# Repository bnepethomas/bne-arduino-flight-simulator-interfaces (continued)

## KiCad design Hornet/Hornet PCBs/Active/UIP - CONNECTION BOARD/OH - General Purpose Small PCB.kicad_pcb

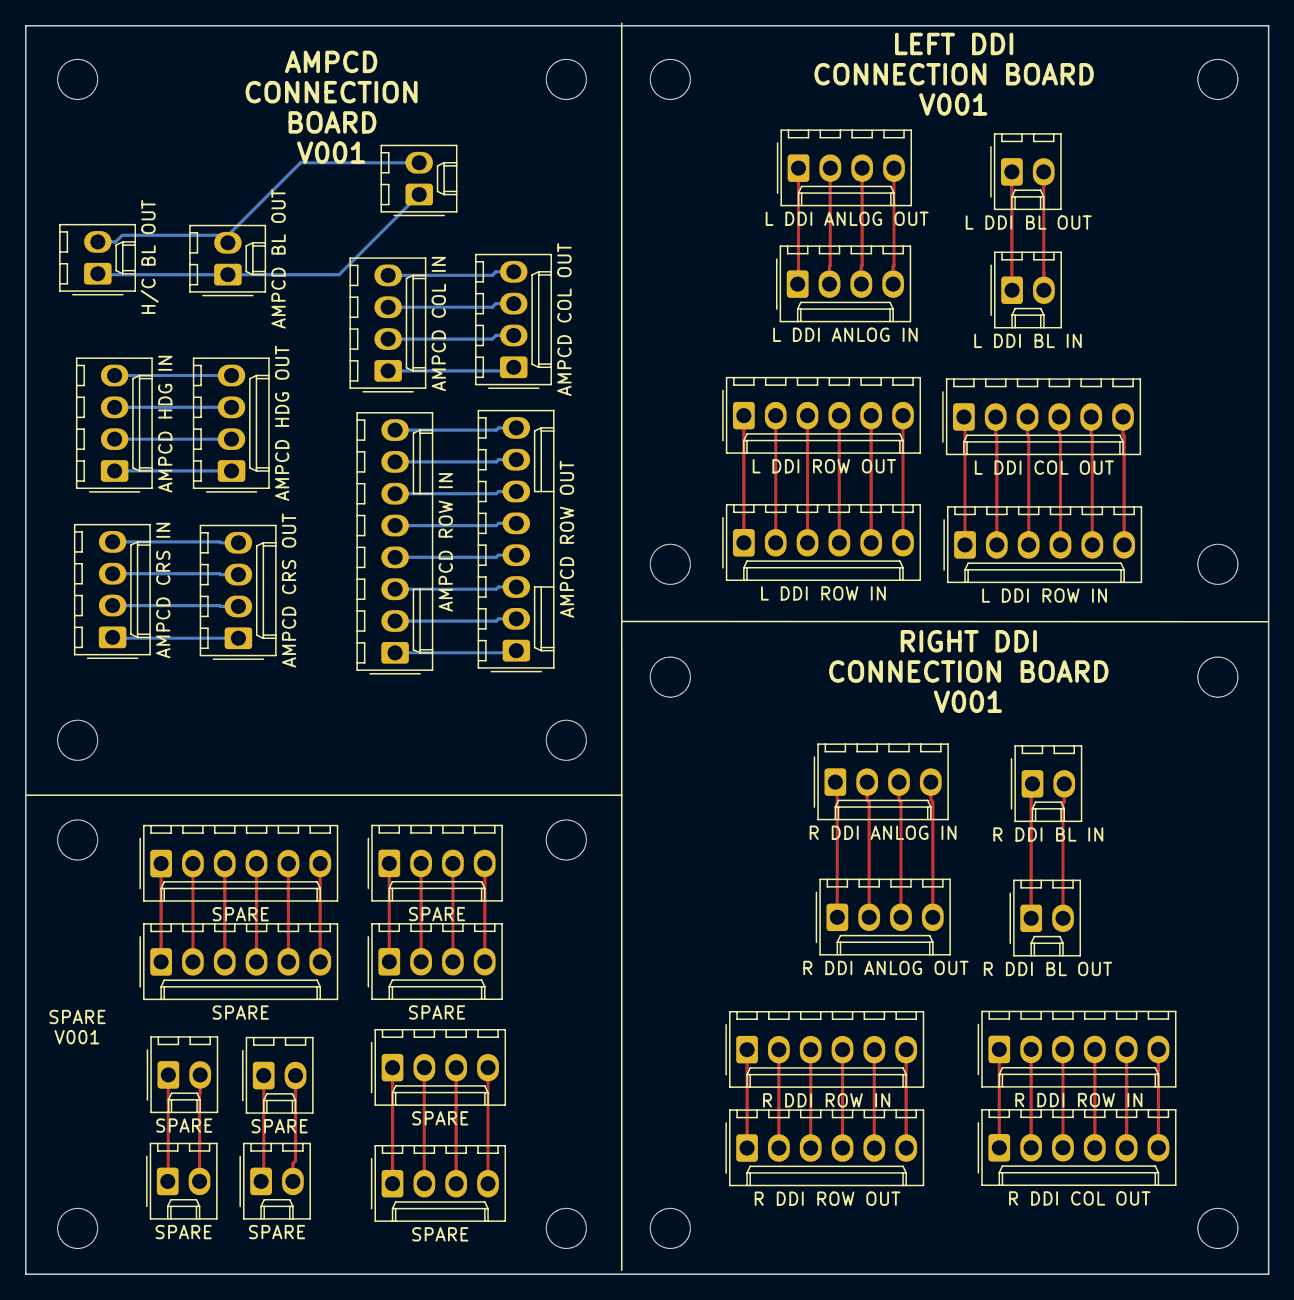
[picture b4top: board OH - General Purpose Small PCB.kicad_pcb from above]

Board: 2 copper layers, 99.2 x 99.6 mm, 53 parts (0 on the bottom side), 76 nets.

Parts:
H1, H2, H3, H4, H5, H6, H7, H8, H9, H10, H11, H12, H13, H14, H15, H16: MountingHole; MountingHole_3.2mm_M3
J1: AMPCD COL IN; Molex_1x04_P2.54mm_Vertical
J2: AMPCD COL OUT; Molex_1x04_P2.54mm_Vertical
J3: H/C BL OUT; Molex_1x02_P2.54mm_Vertical
J4, J12, J34, J37: SPARE; Molex_1x02_P2.54mm_Vertical
J5: AMPCD CRS IN; Molex_1x04_P2.54mm_Vertical
J6: AMPCD HDG IN; Molex_1x04_P2.54mm_Vertical
J7, J8, J14, J16: SPARE; Molex_1x04_P2.54mm_Vertical
J9: AMPCD BL IN; Molex_1x02_P2.54mm_Vertical
J10, J18: SPARE; Molex_1x06_P2.54mm_Vertical
J11: L DDI ANLOG IN; Molex_1x04_P2.54mm_Vertical
J13: AMPCD BL OUT; Molex_1x02_P2.54mm_Vertical
J15: L DDI ANLOG OUT; Molex_1x04_P2.54mm_Vertical
J17: AMPCD ROW IN; Molex_1x08_P2.54mm_Vertical
J19: AMPCD ROW OUT; Molex_1x08_P2.54mm_Vertical
J20: AMPCD CRS OUT; Molex_1x04_P2.54mm_Vertical
J21, J26: L DDI ROW IN; Molex_1x06_P2.54mm_Vertical
J22: L DDI BL IN; Molex_1x02_P2.54mm_Vertical
J23, J27: R DDI ROW IN; Molex_1x06_P2.54mm_Vertical
J24: L DDI BL OUT; Molex_1x02_P2.54mm_Vertical
J25: L DDI ROW OUT; Molex_1x06_P2.54mm_Vertical
J28: R DDI ROW OUT; Molex_1x06_P2.54mm_Vertical
J29: R DDI COL OUT; Molex_1x06_P2.54mm_Vertical
J30: R DDI BL IN; Molex_1x02_P2.54mm_Vertical
J31: R DDI ANLOG IN; Molex_1x04_P2.54mm_Vertical
J32: L DDI COL OUT; Molex_1x06_P2.54mm_Vertical
J33: AMPCD HDG OUT; Molex_1x04_P2.54mm_Vertical
J35: R DDI BL OUT; Molex_1x02_P2.54mm_Vertical
J36: R DDI ANLOG OUT; Molex_1x04_P2.54mm_Vertical

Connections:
unnamed: J1.1, J2.1
unnamed: J1.2, J2.2
unnamed: J1.3, J2.3
unnamed: J1.4, J2.4
unnamed: J10.1, J18.1
unnamed: J10.2, J18.2
unnamed: J10.3, J18.3
unnamed: J10.4, J18.4
unnamed: J10.5, J18.5
unnamed: J10.6, J18.6
unnamed: J11.1, J15.1
unnamed: J11.2, J15.2
unnamed: J11.3, J15.3
unnamed: J11.4, J15.4
unnamed: J4.1, J12.1
unnamed: J4.2, J12.2
unnamed: J3.1, J9.1, J13.1
unnamed: J3.2, J9.2, J13.2
unnamed: J7.1, J14.1
unnamed: J7.2, J14.2
unnamed: J7.3, J14.3
unnamed: J7.4, J14.4
unnamed: J8.1, J16.1
unnamed: J8.2, J16.2
unnamed: J8.3, J16.3
unnamed: J8.4, J16.4
unnamed: J17.1, J19.1
unnamed: J17.2, J19.2
unnamed: J17.3, J19.3
unnamed: J17.4, J19.4
unnamed: J17.5, J19.5
unnamed: J17.6, J19.6
unnamed: J17.7, J19.7
unnamed: J17.8, J19.8
unnamed: J5.1, J20.1
unnamed: J5.2, J20.2
unnamed: J5.3, J20.3
unnamed: J5.4, J20.4
unnamed: J21.1, J32.1
unnamed: J21.2, J32.2
unnamed: J21.3, J32.3
unnamed: J21.4, J32.4
unnamed: J21.5, J32.5
unnamed: J21.6, J32.6
unnamed: J22.1, J24.1
unnamed: J22.2, J24.2
unnamed: J23.1, J28.1
unnamed: J23.2, J28.2
unnamed: J23.3, J28.3
unnamed: J23.4, J28.4
unnamed: J23.5, J28.5
unnamed: J23.6, J28.6
unnamed: J25.1, J26.1
unnamed: J25.2, J26.2
unnamed: J25.3, J26.3
unnamed: J25.4, J26.4
unnamed: J25.5, J26.5
unnamed: J25.6, J26.6
unnamed: J27.1, J29.1
unnamed: J27.2, J29.2
unnamed: J27.3, J29.3
unnamed: J27.4, J29.4
unnamed: J27.5, J29.5
unnamed: J27.6, J29.6
unnamed: J30.1, J35.1
unnamed: J30.2, J35.2
unnamed: J31.1, J36.1
unnamed: J31.2, J36.2
unnamed: J31.3, J36.3
unnamed: J31.4, J36.4
unnamed: J6.1, J33.1
unnamed: J6.2, J33.2
unnamed: J6.3, J33.3
unnamed: J6.4, J33.4
unnamed: J34.1, J37.1
unnamed: J34.2, J37.2

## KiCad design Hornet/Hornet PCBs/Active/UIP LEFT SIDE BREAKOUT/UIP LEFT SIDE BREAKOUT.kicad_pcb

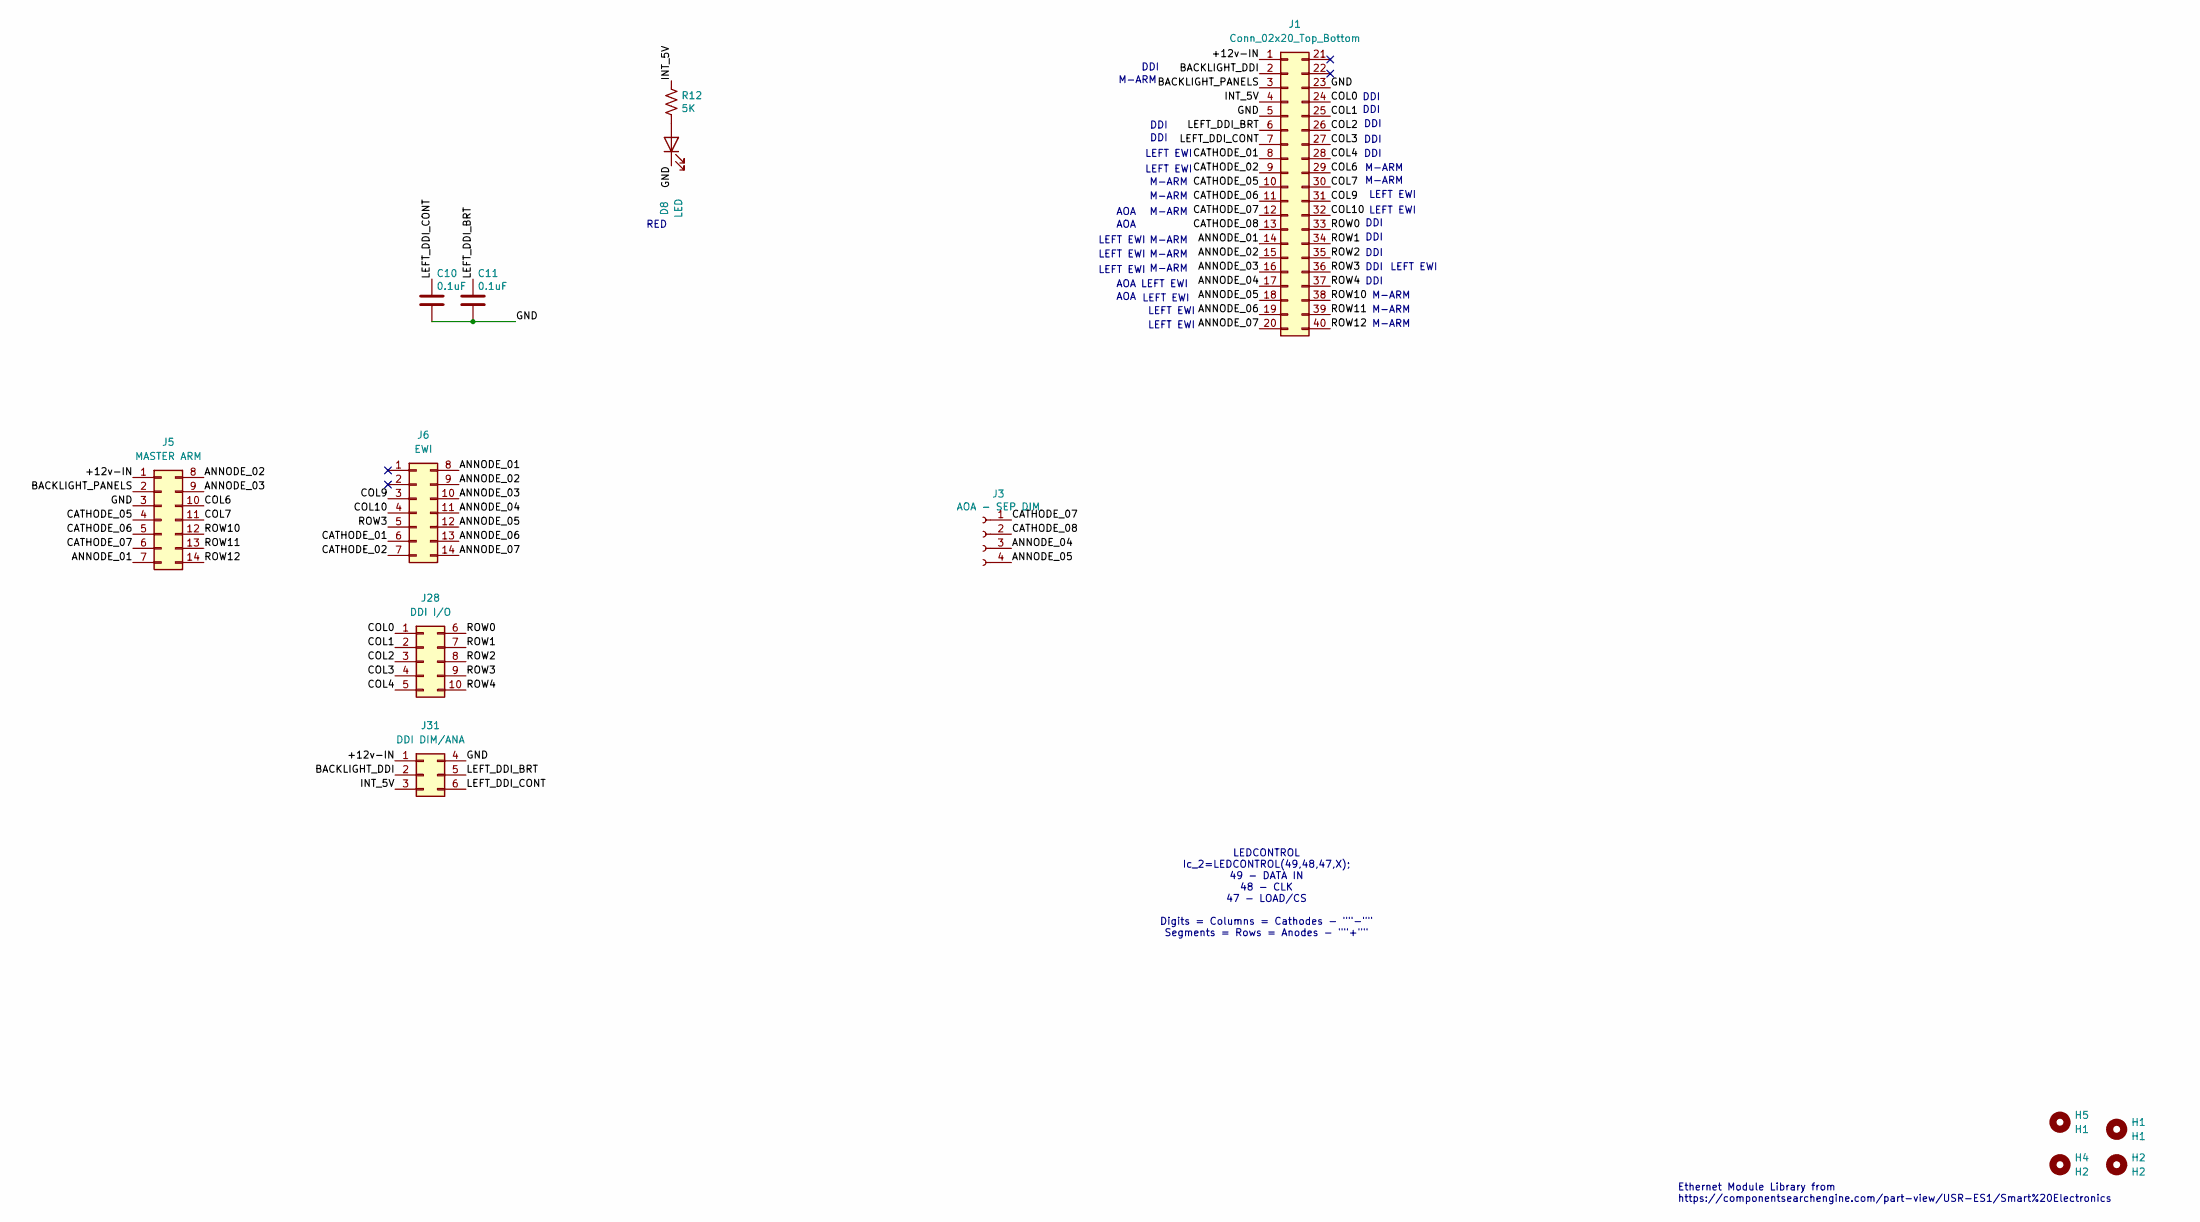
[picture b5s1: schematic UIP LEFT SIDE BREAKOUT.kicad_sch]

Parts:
C10, C11: 0.1uF; C_0805_2012Metric
D8: LED; LED_0805_2012Metric
H1, H5: H1; MountingHole_2.5mm
H2, H4: H2; MountingHole_2.5mm
J1: Conn_02x20_Top_Bottom; IDC-Header_2x20_P2.54mm_Vertical
J3: AOA - SEP DIM; Molex_KK-254_AE-6410-04A_1x04_P2.54mm_Vertical
J5: MASTER ARM; IDC-Header_2x07_P2.54mm_Vertical
J6: EWI; IDC-Header_2x07_P2.54mm_Vertical
J28: DDI I/O; IDC-Header_2x05_P2.54mm_Vertical
J31: DDI DIM/ANA; IDC-Header_2x03_P2.54mm_Vertical
R12: 5K; R_0805_2012Metric

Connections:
/+12v-IN: J1.1, J5.1, J31.1
/ANNODE_01: J1.14, J5.7, J6.8
/ANNODE_02: J1.15, J5.8, J6.9
/ANNODE_03: J1.16, J5.9, J6.10
/ANNODE_04: J1.17, J3.3, J6.11
/ANNODE_05: J1.18, J3.4, J6.12
/ANNODE_06: J1.19, J6.13
/ANNODE_07: J1.20, J6.14
/BACKLIGHT_DDI: J1.2, J31.2
/BACKLIGHT_PANELS: J1.3, J5.2
/CATHODE_01: J1.8, J6.6
/CATHODE_02: J1.9, J6.7
/CATHODE_05: J1.10, J5.4
/CATHODE_06: J1.11, J5.5
/CATHODE_07: J1.12, J3.1, J5.6
/CATHODE_08: J1.13, J3.2
/COL0: J1.24, J28.1
/COL1: J1.25, J28.2
/COL2: J1.26, J28.3
/COL3: J1.27, J28.4
/COL4: J1.28, J28.5
/COL6: J1.29, J5.10
/COL7: J1.30, J5.11
/COL9: J1.31, J6.3
/COL10: J1.32, J6.4
/GND: C10.2, C11.2, D8.1 (K), J1.5, J1.23, J5.3, J31.4
/INT_5V: J1.4, J31.3, R12.1
/LEFT_DDI_BRT: C11.1, J1.6, J31.5
/LEFT_DDI_CONT: C10.1, J1.7, J31.6
/ROW0: J1.33, J28.6
/ROW1: J1.34, J28.7
/ROW2: J1.35, J28.8
/ROW3: J1.36, J6.5, J28.9
/ROW4: J1.37, J28.10
/ROW10: J1.38, J5.12
/ROW11: J1.39, J5.13
/ROW12: J1.40, J5.14
unnamed: D8.2 (A), R12.2

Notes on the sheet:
M-ARM
LEFT EWI
DDI
AOA
Ethernet Module Library from https://componentsearchengine.com/part-view/USR-ES1/Smart%20Electronics
LEDCONTROL Ic_2=LEDCONTROL(49,48,47,X); 49 - DATA IN 48 - CLK 47 - LOAD/CS Digits = Columns = Cathodes - ""-"" Segments = Rows = Anodes - ""+""
RED

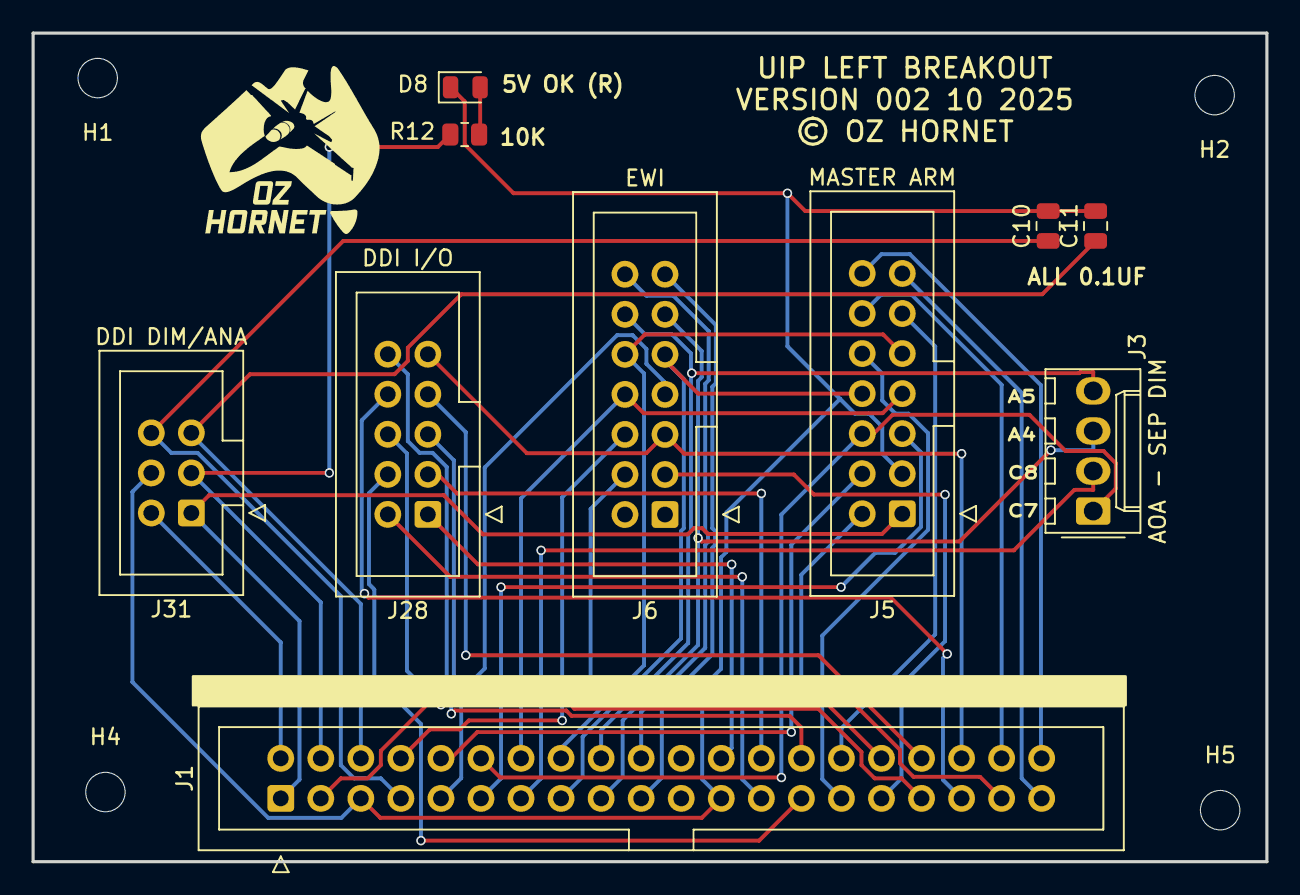
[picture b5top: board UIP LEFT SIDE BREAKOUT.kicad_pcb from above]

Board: 2 copper layers, 78.2 x 52.6 mm, 14 parts (0 on the bottom side), 38 nets.

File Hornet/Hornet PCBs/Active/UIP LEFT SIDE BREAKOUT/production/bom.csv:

Designator,Footprint,Quantity,Value,LCSC Part #
"C10, C11",0805,2,0.1uF,
D8,0805,1,LED,
"H1, H5",MountingHole_2.5mm,2,H1,
"H2, H4",MountingHole_2.5mm,2,H2,
J1,IDC-Header_2x20_P2.54mm_Vertical,1,Conn_02x20_Top_Bottom,
J28,IDC-Header_2x05_P2.54mm_Vertical,1,DDI I/O,
J3,Molex_KK-254_AE-6410-04A_1x04_P2.54mm_Vertical,1,AOA - SEP DIM,
J31,IDC-Header_2x03_P2.54mm_Vertical,1,DDI DIM/ANA,
J5,IDC-Header_2x07_P2.54mm_Vertical,1,MASTER ARM,
J6,IDC-Header_2x07_P2.54mm_Vertical,1,EWI,
R12,0805,1,5K,

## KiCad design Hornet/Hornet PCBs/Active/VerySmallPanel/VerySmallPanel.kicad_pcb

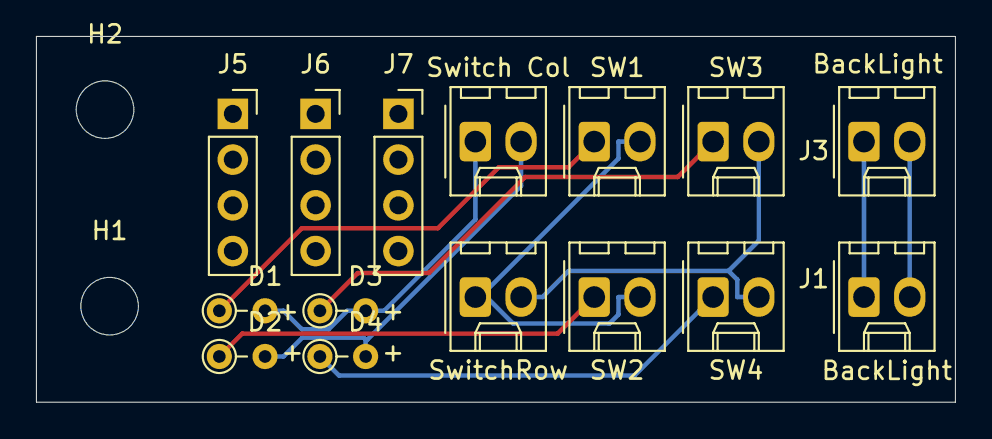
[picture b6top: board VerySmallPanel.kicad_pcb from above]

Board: 2 copper layers, 51.1 x 20.3 mm, 17 parts (0 on the bottom side), 10 nets.

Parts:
D1, D2, D3, D4: 1N4148; PT_R_Axial_DIN0204_L3.6mm_D1.6mm_P2.54mm_Vertical
H1, H2: MountingHole; MountingHole_3.2mm_M3
J1, J3: BackLight; Molex_1x02_P2.54mm_Vertical
J5, J6, J7: Conn_01x04_Female; PinSocket_1x04_P2.54mm_Vertical
SW1: SW1; Molex_1x02_P2.54mm_Vertical
SW2: SW2; Molex_1x02_P2.54mm_Vertical
SW3: SW3; Molex_1x02_P2.54mm_Vertical
SW4: SW4; Molex_1x02_P2.54mm_Vertical
Switch Col: SwitchCol; Molex_1x02_P2.54mm_Vertical
SwitchRow: SwitchRow; Molex_1x02_P2.54mm_Vertical

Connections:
unnamed: D1.1, SW1.1
unnamed: D1.2, D3.2, Switch Col.1
unnamed: D2.1, SW2.1
unnamed: D2.2, D4.2, Switch Col.2
unnamed: D3.1, SW3.1
unnamed: D4.1, SW4.1
unnamed: J1.1, J3.1
unnamed: J1.2, J3.2
unnamed: SW1.2, SW2.2, SwitchRow.1
unnamed: SW3.2, SW4.2, SwitchRow.2

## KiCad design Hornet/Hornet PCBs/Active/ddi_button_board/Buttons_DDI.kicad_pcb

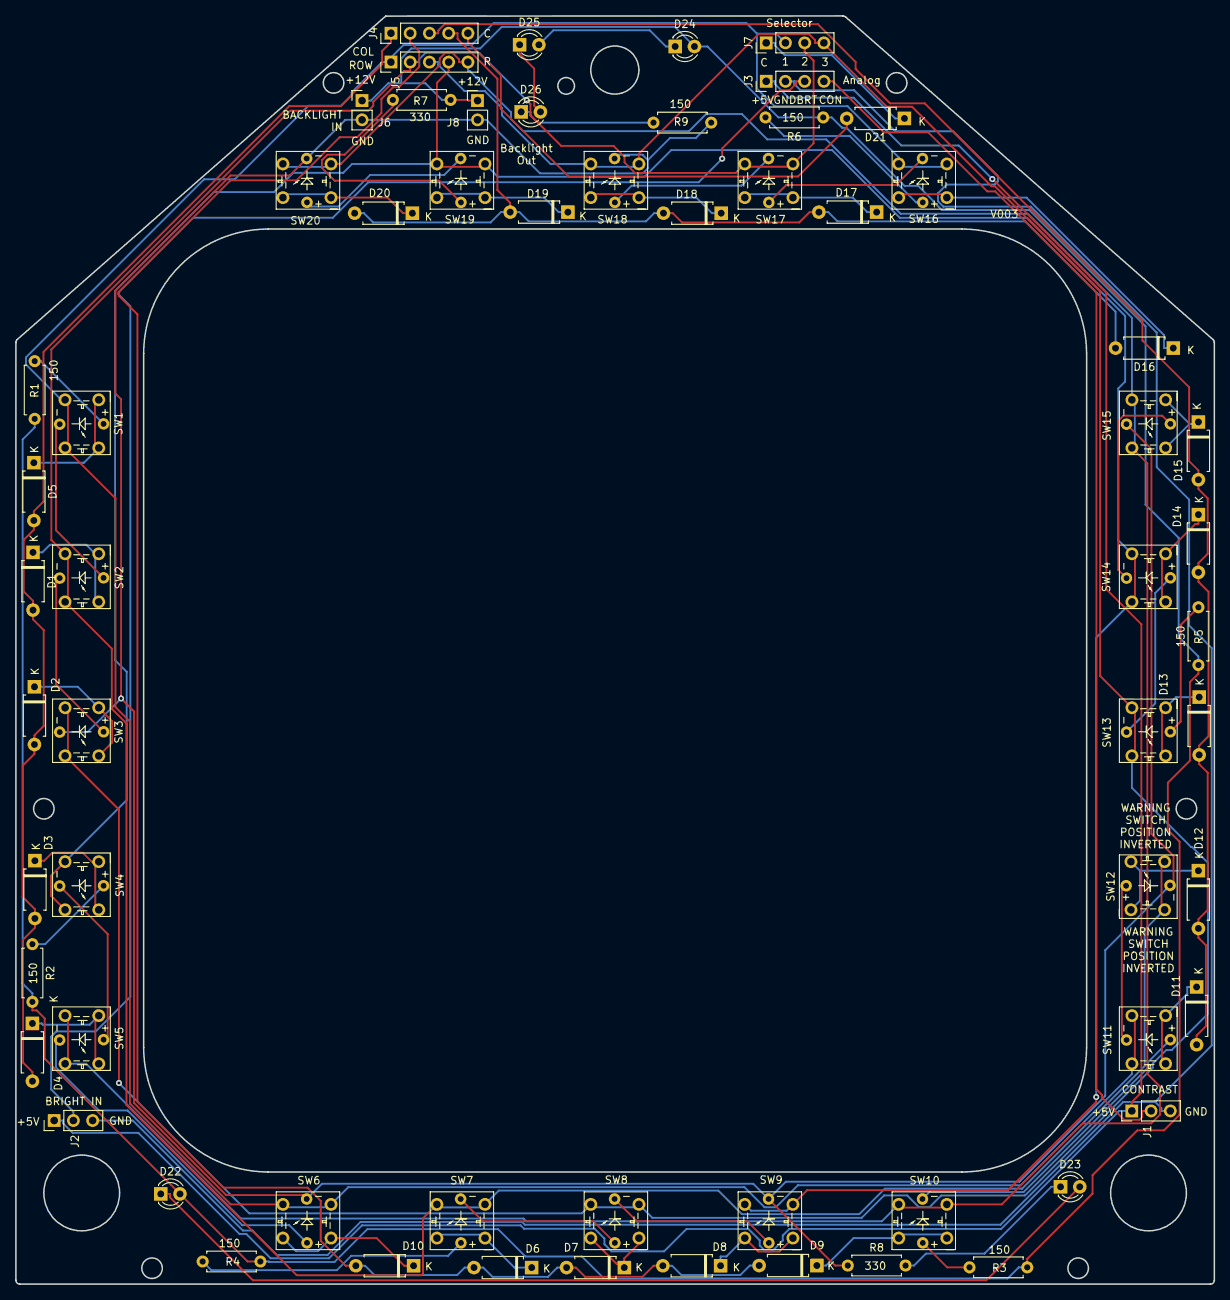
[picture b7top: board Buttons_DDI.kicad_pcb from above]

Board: 2 copper layers, 158.2 x 167.4 mm, 63 parts (0 on the bottom side), 62 nets.

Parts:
D1, D2, D3, D4, D5, D6, D7, D8, D9, D10, D11, D12, D13, D14, D15, D16, D17, D18, D19, D20, D21: D; D_A-405_P7.62mm_Horizontal
D22, D23, D24, D25, D26: LED; LED_D3.0mm
J1, J2: Conn_01x03_Female; PinHeader_1x03_P2.54mm_Vertical
J3, J7: Conn_01x04_Female; PinHeader_1x04_P2.54mm_Vertical
J4, J5: Conn_01x05_Female; PinHeader_1x05_P2.54mm_Vertical
J6, J8: Conn_01x02_Female; PinHeader_1x02_P2.54mm_Vertical
R1, R2, R3, R4, R5, R6, R9: 150; R_Axial_DIN0207_L6.3mm_D2.5mm_P7.62mm_Horizontal
R7, R8: 330; R_Axial_DIN0207_L6.3mm_D2.5mm_P7.62mm_Horizontal
SW1, SW2, SW3, SW4, SW5, SW6, SW7, SW8, SW9, SW10, SW11, SW12, SW13, SW14, SW15, SW16, SW17, SW18, SW19, SW20: 1; PT_Small_Tactile_Switch_With_LED

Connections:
/Ana_Bright: J2.2, J3.3
/Ana_Contrast: J1.2, J3.4
/Analog+5V: J1.1, J2.1, J3.1
/Analog_GND: J1.3, J2.3, J3.2
/Backlight+: D22.2, D24.2, J6.1, J8.1, R1.2, R2.2, R3.2, R4.2, R5.2, R6.2, R7.2
/Col_0: D1.2, D2.2, D3.2, D4.2, D5.2, J4.1
/Col_1: D6.2, D7.2, D8.2, D9.2, D10.2, J4.2
/Col_2: D11.2, D12.2, D13.2, D14.2, D15.2, J4.3
/Col_3: D16.2, D17.2, D18.2, D19.2, D20.2, J4.4
/Col_4: D21.2, J4.5
/Led5Led6: SW5.6, SW6.5
/Led10-11: SW10.6, SW11.5
/Row_0: J5.1, J7.2, SW1.3, SW1.4, SW6.3, SW6.4, SW11.3, SW11.4, SW16.3, SW16.4
/Row_1: J5.2, J7.3, SW2.3, SW2.4, SW7.3, SW7.4, SW12.3, SW12.4, SW17.3, SW17.4
/Row_2: J5.3, J7.4, SW3.3, SW3.4, SW8.3, SW8.4, SW13.3, SW13.4, SW18.3, SW18.4
/Row_3: J5.4, SW4.3, SW4.4, SW9.3, SW9.4, SW14.3, SW14.4, SW19.3, SW19.4
/Row_4: J5.5, SW5.3, SW5.4, SW10.3, SW10.4, SW15.3, SW15.4, SW20.3, SW20.4
GND: J6.2, J8.2, R8.1, R9.1, SW3.6, SW6.6, SW9.6, SW12.6, SW15.6, SW18.6, SW20.6
unnamed: D1.1, SW2.1, SW2.2
unnamed: D2.1, SW3.1, SW3.2
unnamed: D3.1, SW4.1, SW4.2
unnamed: D4.1, SW5.1, SW5.2
unnamed: D5.1, SW1.1, SW1.2
unnamed: D6.1, SW7.1, SW7.2
unnamed: D7.1, SW8.1, SW8.2
unnamed: D8.1, SW9.1, SW9.2
unnamed: D9.1, SW10.1, SW10.2
unnamed: D10.1, SW6.1, SW6.2
unnamed: D11.1, SW11.1, SW11.2
unnamed: D12.1, SW12.1, SW12.2
unnamed: D13.1, SW13.1, SW13.2
unnamed: D14.1, SW14.1, SW14.2
unnamed: D15.1, SW15.1, SW15.2
unnamed: D16.1, SW16.1, SW16.2
unnamed: D17.1, SW17.1, SW17.2
unnamed: D18.1, SW18.1, SW18.2
unnamed: D19.1, SW19.1, SW19.2
unnamed: D20.1, SW20.1, SW20.2
unnamed: D21.1, J7.1
unnamed: D22.1, D23.2
unnamed: D23.1, R8.2
unnamed: D24.1, D25.2
unnamed: D25.1, D26.2
unnamed: D26.1, R9.2
unnamed: R1.1, SW1.5
unnamed: R2.1, SW4.5
unnamed: R3.1, SW10.5
unnamed: R4.1, SW7.5
unnamed: R5.1, SW13.5
unnamed: R6.1, SW16.5
unnamed: R7.1, SW19.5
unnamed: SW1.6, SW2.5
unnamed: SW2.6, SW3.5
unnamed: SW4.6, SW5.5
unnamed: SW7.6, SW8.5
unnamed: SW8.6, SW9.5
unnamed: SW11.6, SW12.5
unnamed: SW13.6, SW14.5
unnamed: SW14.6, SW15.5
unnamed: SW16.6, SW17.5
unnamed: SW17.6, SW18.5
unnamed: SW19.6, SW20.5

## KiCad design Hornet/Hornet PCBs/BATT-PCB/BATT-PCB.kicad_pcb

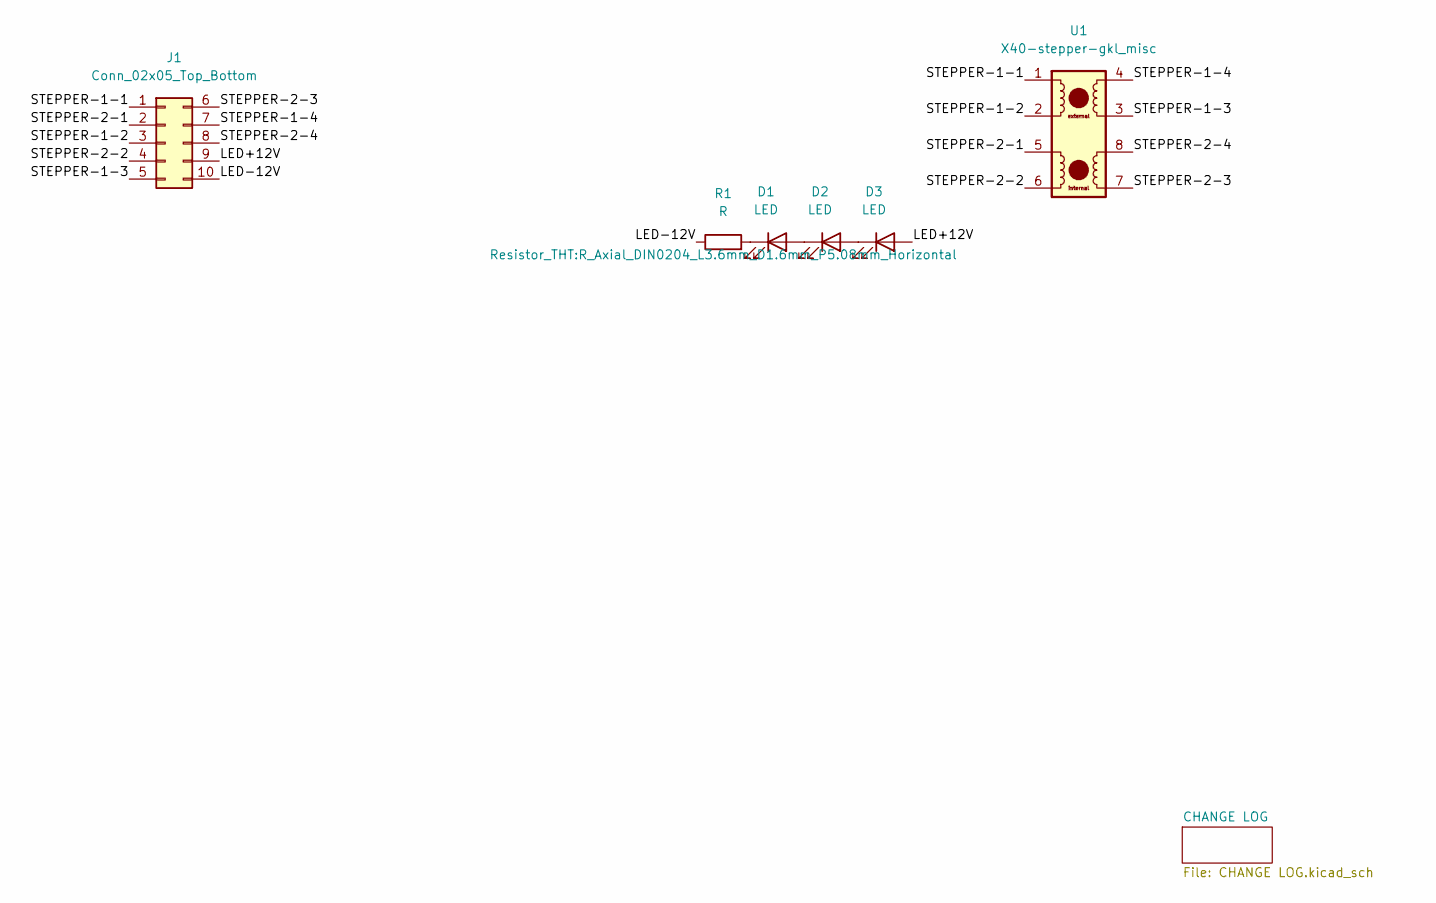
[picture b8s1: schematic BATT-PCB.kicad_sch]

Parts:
D1, D2, D3: LED; LED_D3.0mm
J1: Conn_02x05_Top_Bottom; PinHeader_2x05_P2.54mm_Vertical
R1: R; R_Axial_DIN0204_L3.6mm_D1.6mm_P5.08mm_Horizontal
U1: X40-stepper-gkl_misc; X40-stepper

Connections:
/LED+12V: D3.2 (A), J1.9
/LED-12V: J1.10, R1.1
/STEPPER-1-1: J1.1, U1.1
/STEPPER-1-2: J1.3, U1.2
/STEPPER-1-3: J1.5, U1.3
/STEPPER-1-4: J1.7, U1.4
/STEPPER-2-1: J1.2, U1.5
/STEPPER-2-2: J1.4, U1.6
/STEPPER-2-3: J1.6, U1.7
/STEPPER-2-4: J1.8, U1.8
unnamed: D1.1 (K), R1.2
unnamed: D1.2 (A), D2.1 (K)
unnamed: D2.2 (A), D3.1 (K)

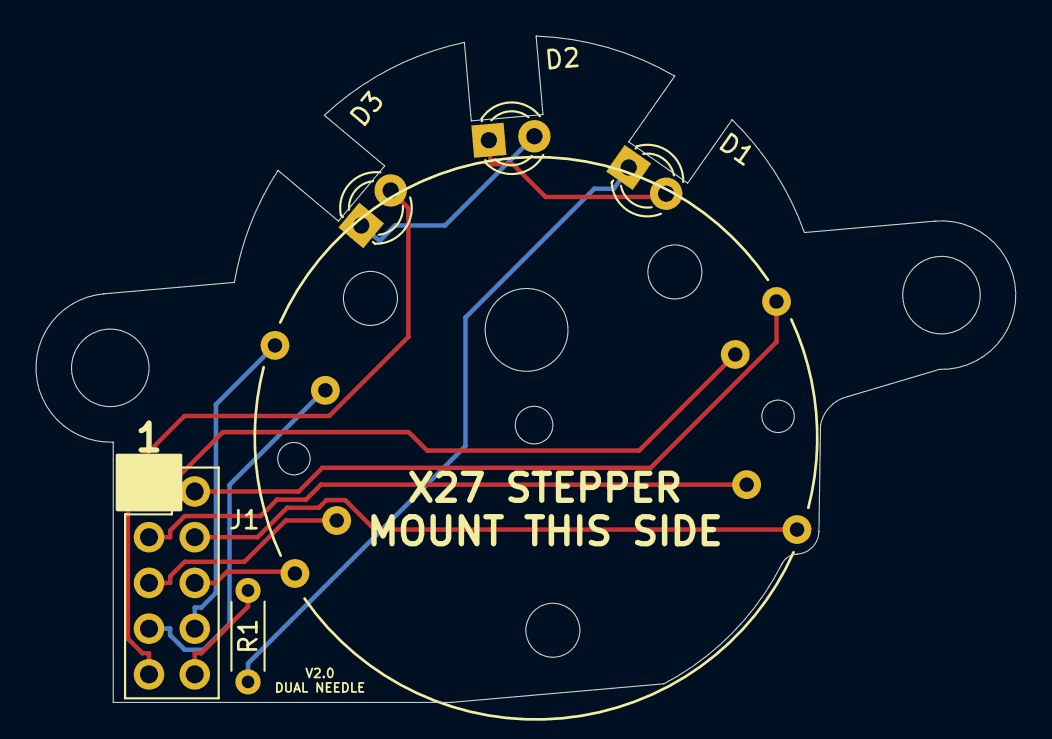
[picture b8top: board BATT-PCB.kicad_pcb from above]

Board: 2 copper layers, 54.4 x 37.0 mm, 6 parts (1 on the bottom side), 13 nets.
